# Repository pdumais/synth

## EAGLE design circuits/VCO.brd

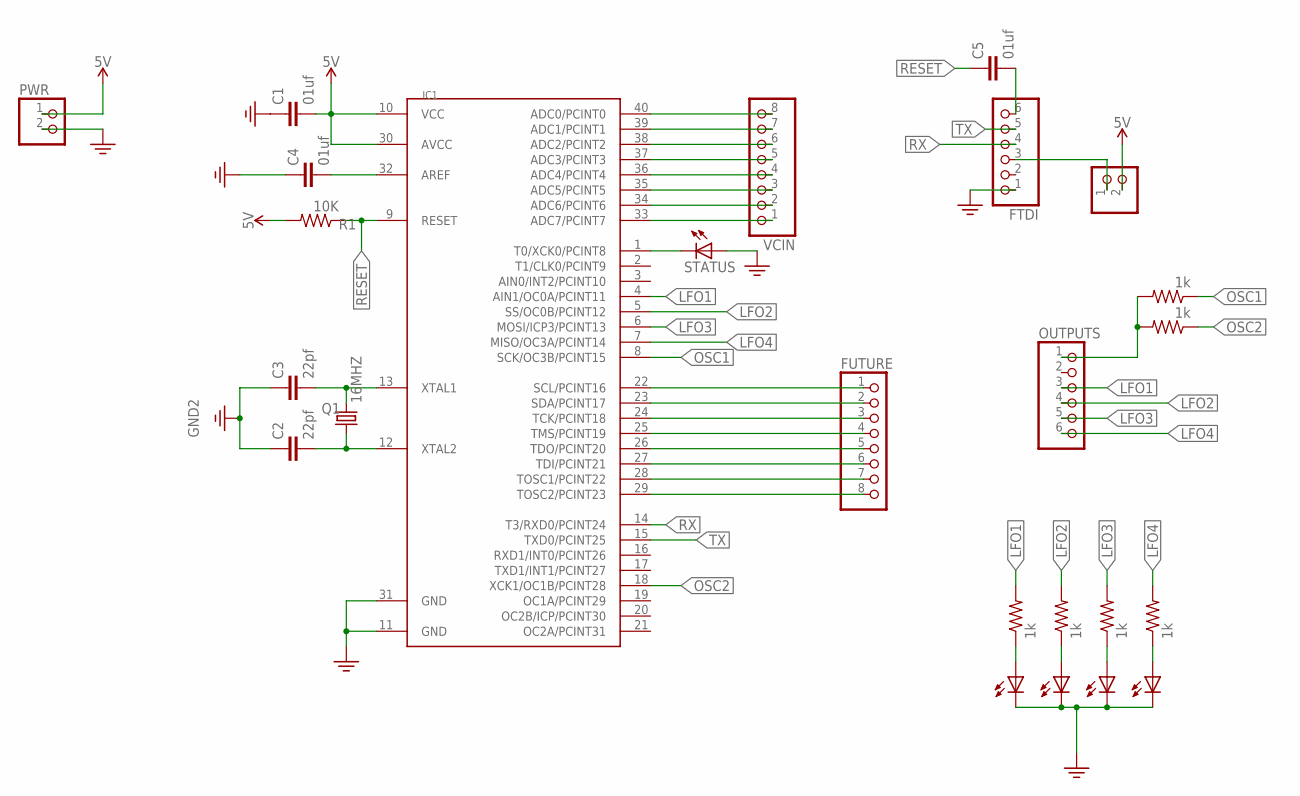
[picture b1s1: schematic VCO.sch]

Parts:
C1, C4, C5: 01uf; C025-024X044
C2, C3: 22pf; C025-024X044
FTDI: PINHD-1X6; 1X06
FUTURE: PINHD-1X8BIG; 1X08-BIG
IC1: MEGA1284P; DIL40
LFO1, LFO2, LFO3, LFO4: LED5MM
OUTPUTS: PINHD-1X6; 1X06
PWR, PWR1: PINHD-1X2; 1X02
Q1: 16MHZ; HC49/S
R1: 10K; 0207/12
R2, R3, R4, R5, R6, R7: 1k; 0207/12
STATUS: LED5MM
VCIN: PINHD-1X8; 1X08

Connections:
3.3V: C1.1, C2.1, C3.1, C4.1, FTDI.1, IC1.11 (GND), IC1.31 (GND), LFO1.K (C), LFO2.K (C), LFO3.K (C), LFO4.K (C), PWR.2, STATUS.A
LFO1: IC1.4 (AIN1/OC0A/PCINT11), OUTPUTS.3, R4.2
LFO2: IC1.5 (SS/OC0B/PCINT12), OUTPUTS.4, R3.2
LFO3: IC1.6 (MOSI/ICP3/PCINT13), OUTPUTS.5, R2.2
LFO4: IC1.7 (MISO/OC3A/PCINT14), OUTPUTS.6, R5.2
unnamed: LFO1.A, R4.1
unnamed: IC1.40 (ADC0/PCINT0), VCIN.8
unnamed: IC1.39 (ADC1/PCINT1), VCIN.7
unnamed: IC1.38 (ADC2/PCINT2), VCIN.6
unnamed: IC1.37 (ADC3/PCINT3), VCIN.5
unnamed: IC1.36 (ADC4/PCINT4), VCIN.4
unnamed: IC1.35 (ADC5/PCINT5), VCIN.3
unnamed: IC1.34 (ADC6/PCINT6), VCIN.2
unnamed: IC1.33 (ADC7/PCINT7), VCIN.1
unnamed: C3.2, IC1.13 (XTAL1), Q1.2
unnamed: C2.2, IC1.12 (XTAL2), Q1.1
unnamed: LFO2.A, R3.1
unnamed: C4.2, IC1.32 (AREF)
unnamed: C5.2, FTDI.6
unnamed: LFO3.A, R2.1
unnamed: LFO4.A, R5.1
unnamed: OUTPUTS.1, R6.2, R7.2
unnamed: FUTURE.1, IC1.22 (SCL/PCINT16)
unnamed: FUTURE.2, IC1.23 (SDA/PCINT17)
unnamed: FUTURE.3, IC1.24 (TCK/PCINT18)
unnamed: FUTURE.4, IC1.25 (TMS/PCINT19)
unnamed: FUTURE.5, IC1.26 (TDO/PCINT20)
unnamed: FTDI.3, PWR1.1
unnamed: IC1.1 (T0/XCK0/PCINT8), STATUS.K (C)
unnamed: FUTURE.6, IC1.27 (TDI/PCINT21)
unnamed: FUTURE.7, IC1.28 (TOSC1/PCINT22)
unnamed: FUTURE.8, IC1.29 (TOSC2/PCINT23)
OSC1: IC1.8 (SCK/OC3B/PCINT15), R6.1
OSC2: IC1.18 (XCK1/OC1B/PCINT28), R7.1
RESET: C5.1, IC1.9 (RESET), R1.1
RX: FTDI.4, IC1.14 (T3/RXD0/PCINT24)
TX: FTDI.5, IC1.15 (TXD0/PCINT25)
VDD: C1.2, IC1.10 (VCC), IC1.30 (AVCC), PWR.1, PWR1.2, R1.2

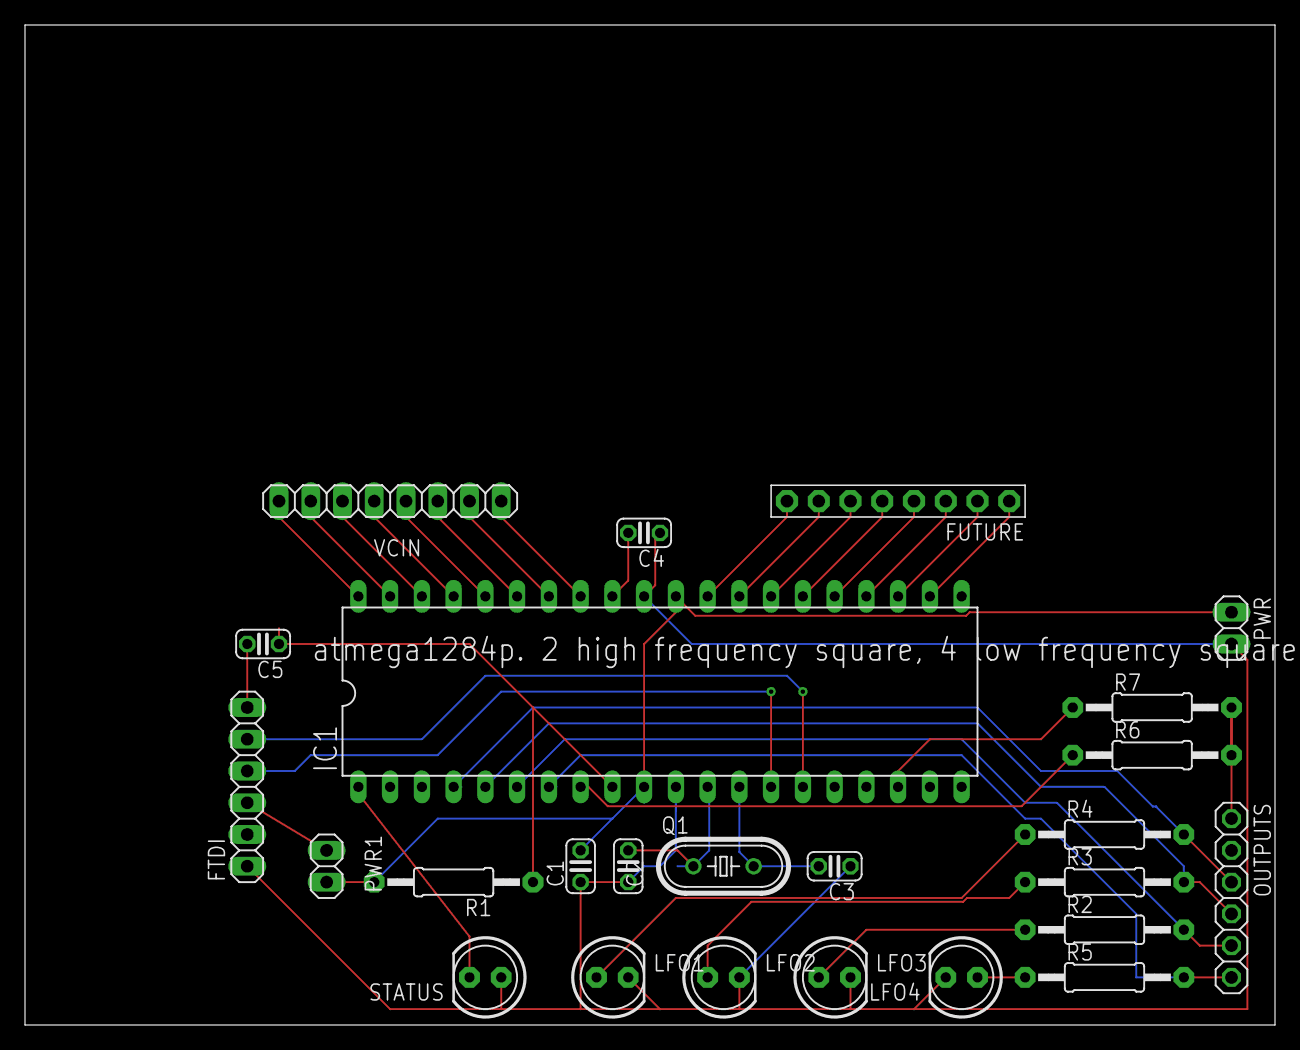
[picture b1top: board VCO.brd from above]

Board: 2 copper layers, 100.0 x 80.0 mm, 25 parts (0 on the bottom side), 38 nets.

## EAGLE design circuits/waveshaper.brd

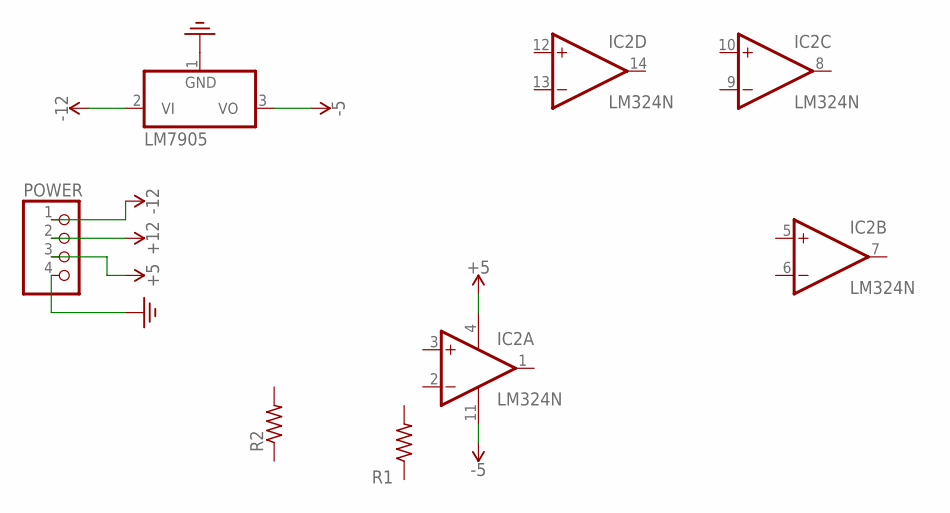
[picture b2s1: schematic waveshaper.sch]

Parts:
IC2: LM324N; DIL14
LM7905: 7905T; TO220H
POWER: PINHD-1X4; 1X04
R1, R2: R-US_0207/12; 0207/12

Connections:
3.3V: LM7905.1 (GND), POWER.4
VDD: IC2.4 (V+), IC2.11 (V-), LM7905.2 (VI), LM7905.3 (VO), POWER.1, POWER.2, POWER.3

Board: 2 copper layers, 5 parts (0 on the bottom side), 2 nets, no tracks yet.

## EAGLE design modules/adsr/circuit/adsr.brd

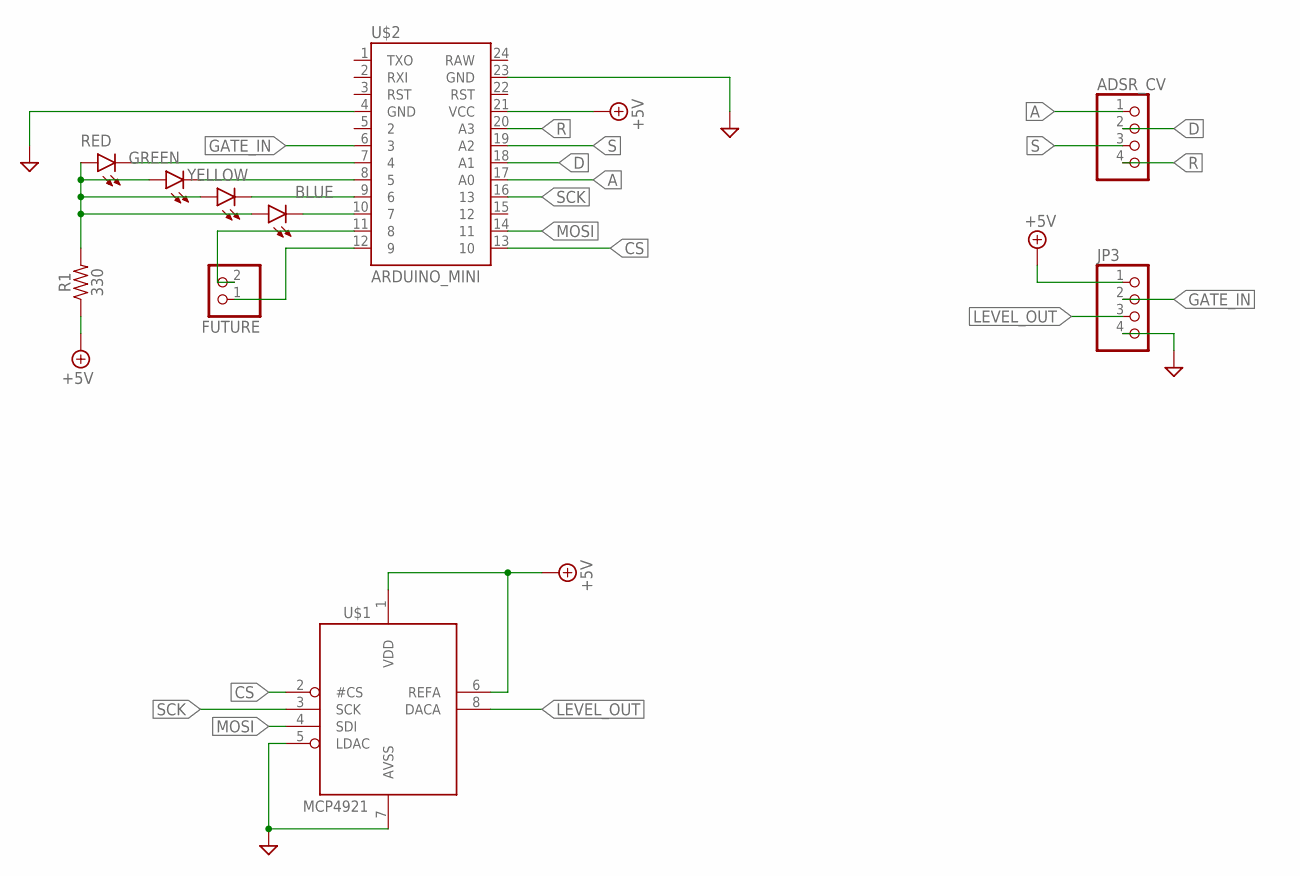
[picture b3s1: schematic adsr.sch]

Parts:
ADSR_CV: PINHD-1X4; 1X04
BLUE: LED-5MM-KIT-NO-SILK; LED_5MM-KIT-NO-SILK
FUTURE: PINHD-1X2; 1X02
GREEN: LED-5MM-KIT-NO-SILK; LED_5MM-KIT-NO-SILK
JP3: PINHD-1X4; 1X04
R1: 330; AXIAL-0.3
RED: LED-5MM-KIT-NO-SILK; LED_5MM-KIT-NO-SILK
U$1: MCP4921; DIL08
U$2: ARDUINO_MINI
YELLOW: LED-5MM-KIT-NO-SILK; LED_5MM-KIT-NO-SILK

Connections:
+5V: JP3.1, R1.P$1 (1), U$1.1 (VDD), U$1.6 (REFA), U$2.21 (VCC)
A: ADSR_CV.1, U$2.17 (A0)
CS: U$1.2 (#CS), U$2.13 (10)
D: ADSR_CV.2, U$2.18 (A1)
GATE_IN: JP3.2, U$2.6 (3)
GND: JP3.4, U$1.5 (LDAC), U$1.7 (AVSS), U$2.4 (GND), U$2.23 (GND)
LEVEL_OUT: JP3.3, U$1.8 (DACA)
MOSI: U$1.4 (SDI), U$2.14 (11)
unnamed: BLUE.K (C), U$2.10 (7)
unnamed: U$2.9 (6), YELLOW.K (C)
unnamed: GREEN.K (C), U$2.8 (5)
unnamed: RED.K (C), U$2.7 (4)
unnamed: BLUE.A, GREEN.A, R1.P$2 (2), RED.A, YELLOW.A
unnamed: FUTURE.2, U$2.11 (8)
unnamed: FUTURE.1, U$2.12 (9)
R: ADSR_CV.4, U$2.20 (A3)
S: ADSR_CV.3, U$2.19 (A2)
SCK: U$1.3 (SCK), U$2.16 (13)

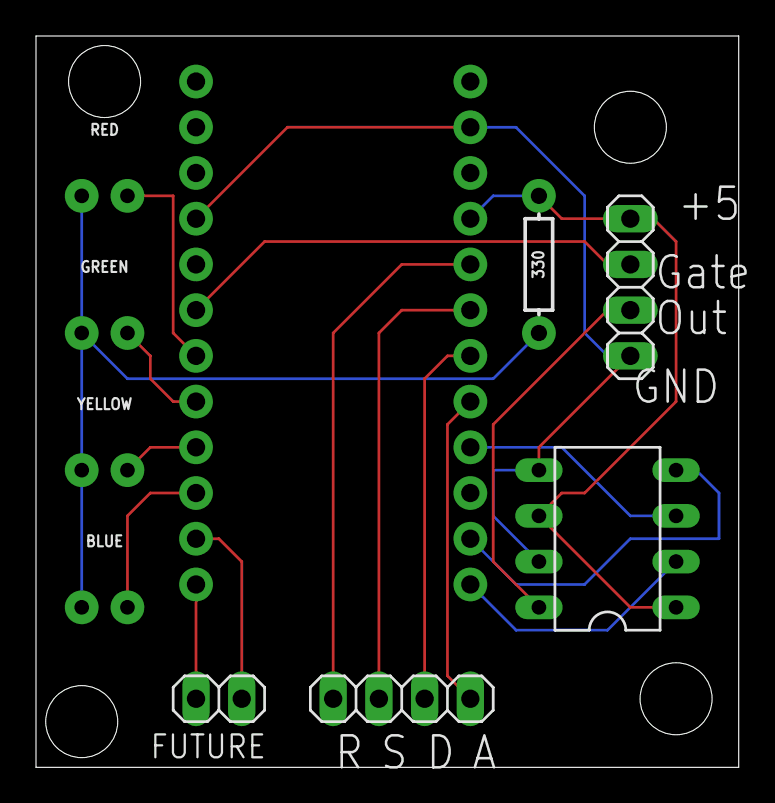
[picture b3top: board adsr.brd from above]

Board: 2 copper layers, 39.0 x 40.6 mm, 10 parts (0 on the bottom side), 18 nets.

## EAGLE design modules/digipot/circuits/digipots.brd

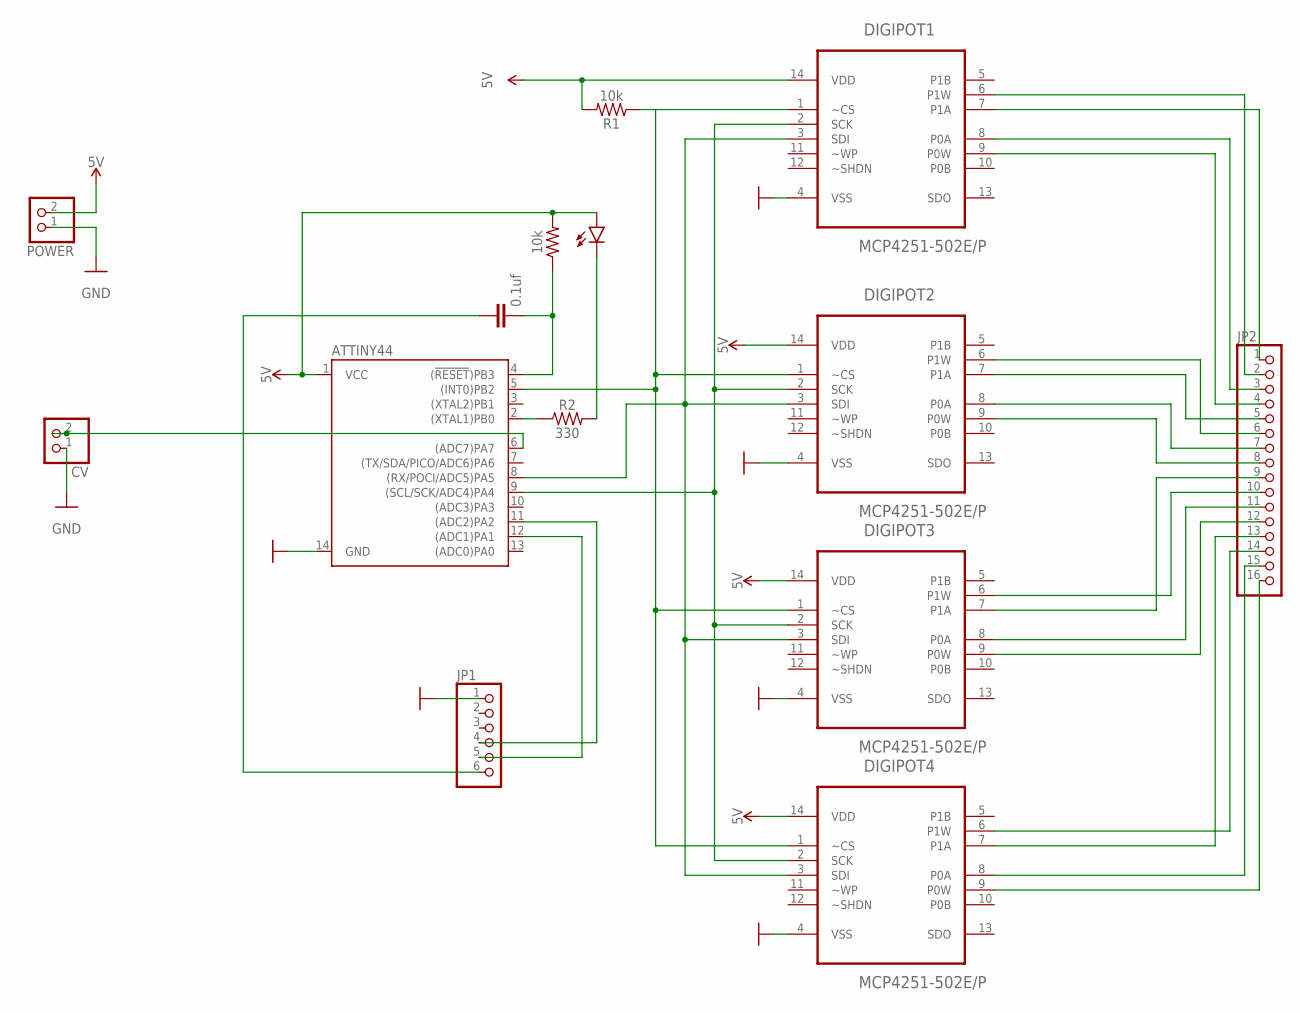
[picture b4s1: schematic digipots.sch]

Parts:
ATTINY44: ATTINY84ATTINY84-20PU; DIP14
C2: 0.1uf; C025-024X044
CV: PINHD-1X2; 1X02
D1: LED-5MM-KIT-NO-SILK; LED_5MM-KIT-NO-SILK
DIGIPOT1, DIGIPOT2, DIGIPOT3, DIGIPOT4: MCP4251-502E/P; DIP254P762X533-14
JP1: PINHD-1X6; 1X06
JP2: PINHD-1X16; 1X16
POWER: PINHD-1X2; 1X02
R1, R3: 10k; AXIAL-0.3
R2: 330; AXIAL-0.3

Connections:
5V: ATTINY44.1 (VCC), D1.A, DIGIPOT1.14 (VDD), DIGIPOT2.14 (VDD), DIGIPOT3.14 (VDD), DIGIPOT4.14 (VDD), POWER.2, R1.P$2 (2), R3.P$2 (2)
GND: ATTINY44.14 (GND), CV.1, DIGIPOT1.4 (VSS), DIGIPOT2.4 (VSS), DIGIPOT3.4 (VSS), DIGIPOT4.4 (VSS), JP1.1, POWER.1
unnamed: DIGIPOT4.9 (P0W), JP2.16
unnamed: DIGIPOT4.8 (P0A), JP2.15
unnamed: DIGIPOT4.6 (P1W), JP2.14
unnamed: DIGIPOT4.7 (P1A), JP2.13
unnamed: DIGIPOT3.9 (P0W), JP2.12
unnamed: DIGIPOT3.8 (P0A), JP2.11
unnamed: DIGIPOT3.6 (P1W), JP2.10
unnamed: DIGIPOT3.7 (P1A), JP2.9
unnamed: DIGIPOT2.9 (P0W), JP2.8
unnamed: DIGIPOT2.8 (P0A), JP2.7
unnamed: DIGIPOT2.7 (P1A), JP2.5
unnamed: DIGIPOT2.6 (P1W), JP2.6
unnamed: DIGIPOT1.9 (P0W), JP2.4
unnamed: DIGIPOT1.8 (P0A), JP2.3
unnamed: DIGIPOT1.7 (P1A), JP2.1
unnamed: DIGIPOT1.6 (P1W), JP2.2
unnamed: ATTINY44.5 ((INT0)PB2), DIGIPOT1.1 (~CS), DIGIPOT2.1 (~CS), DIGIPOT3.1 (~CS), DIGIPOT4.1 (~CS), R1.P$1 (1)
unnamed: ATTINY44.9 ((SCL/SCK/ADC4)PA4), DIGIPOT1.2 (SCK), DIGIPOT2.2 (SCK), DIGIPOT3.2 (SCK), DIGIPOT4.2 (SCK)
unnamed: ATTINY44.2 ((XTAL1)PB0), R2.P$1 (1)
unnamed: ATTINY44.8 ((RX/POCI/ADC5)PA5), DIGIPOT1.3 (SDI), DIGIPOT2.3 (SDI), DIGIPOT3.3 (SDI), DIGIPOT4.3 (SDI)
unnamed: D1.K (C), R2.P$2 (2)
unnamed: ATTINY44.4 ((!RESET!)PB3), C2.2, R3.P$1 (1)
unnamed: ATTINY44.12 ((ADC1)PA1), JP1.5
unnamed: C2.1, JP1.6
unnamed: ATTINY44.11 ((ADC2)PA2), JP1.4
unnamed: ATTINY44.6 ((ADC7)PA7), CV.2

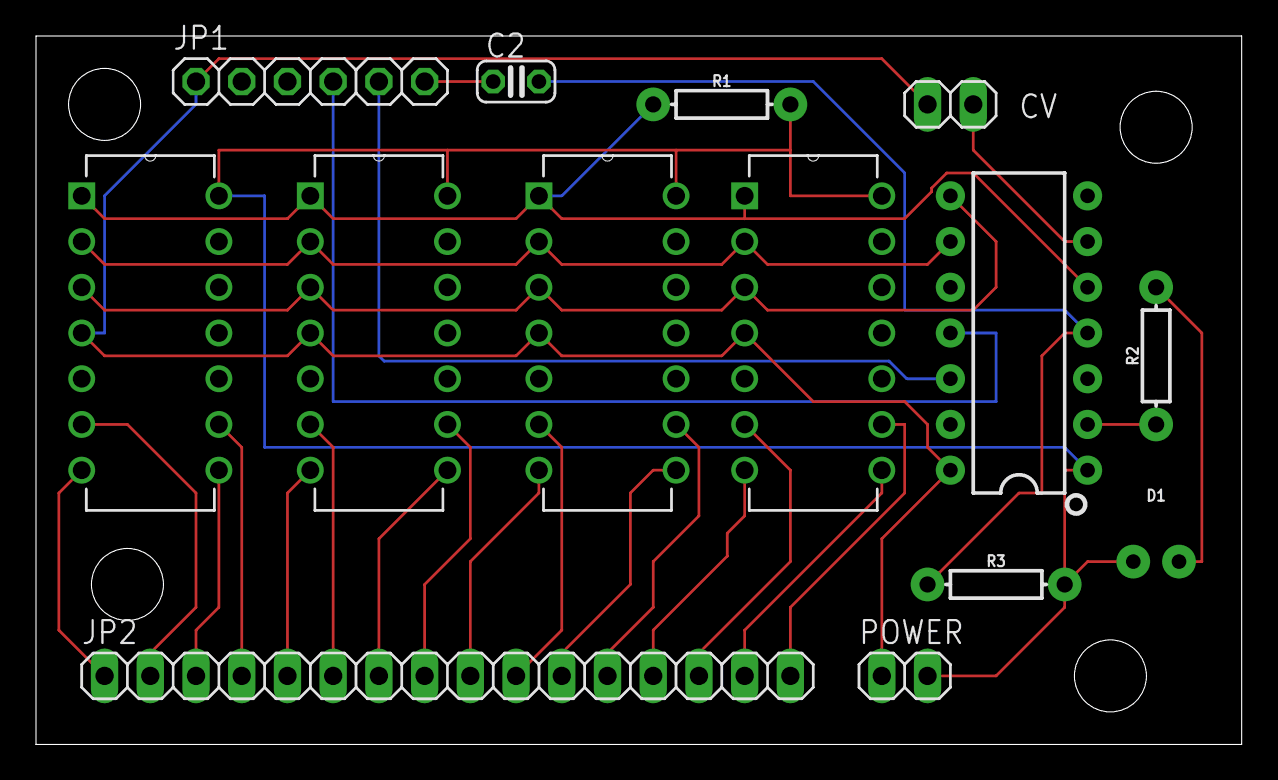
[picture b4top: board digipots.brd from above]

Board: 2 copper layers, 67.0 x 39.4 mm, 14 parts (0 on the bottom side), 28 nets.

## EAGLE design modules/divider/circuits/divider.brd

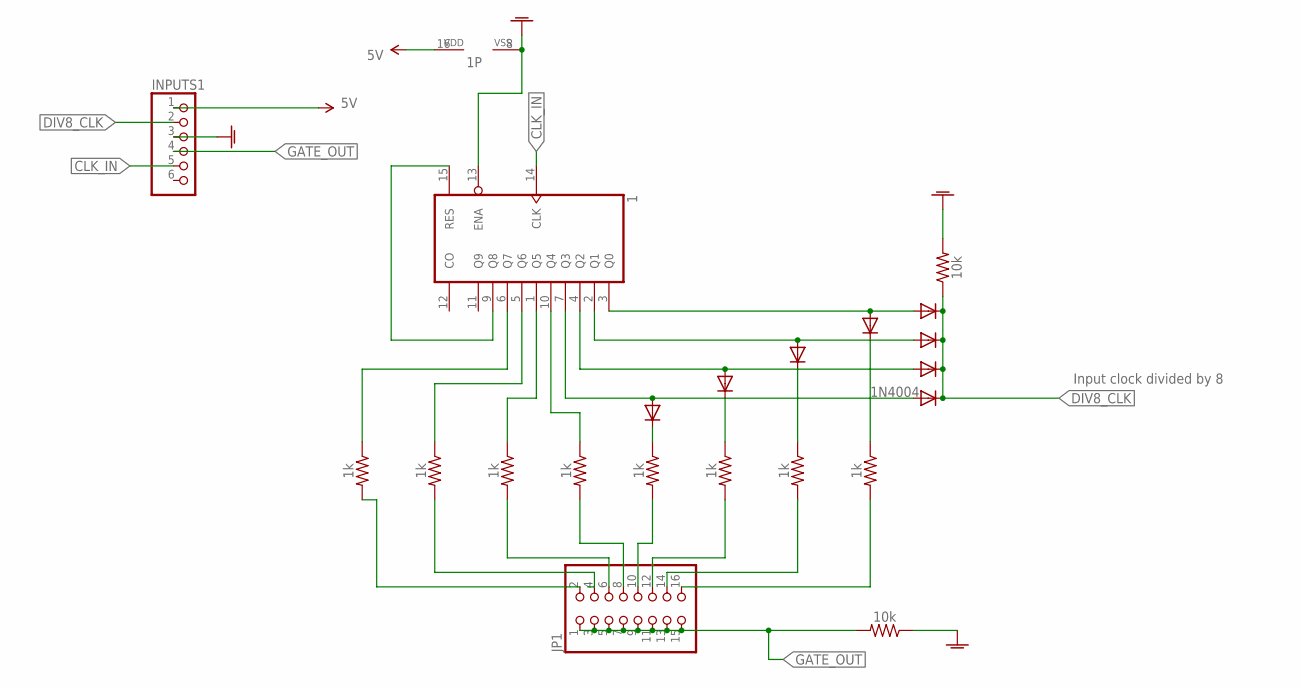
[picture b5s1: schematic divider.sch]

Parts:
1: 4017N; DIL16
D9, D10, D11, D12, D13, D14, D15, D16: 1N4004; DO41-10
INPUTS1: PINHD-1X6; 1X06
JP1: PINHD-2X8; 2X08
R40, R56: 10k; AXIAL-0.3
R48, R49, R50, R51, R52, R53, R54, R55: 1k; AXIAL-0.3

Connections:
5V: 1.16 (VDD), INPUTS1.1
CLK_IN: 1.14 (CLK), INPUTS1.5
DIV8_CLK: D9.C, D10.C, D11.C, D12.C, INPUTS1.2, R40.P$1 (1)
GATE_OUT: INPUTS1.4, JP1.1, JP1.3, JP1.5, JP1.7, JP1.9, JP1.11, JP1.13, JP1.15, R56.P$2 (2)
GND: 1.8 (VSS), 1.13 (ENA)
GNDA: INPUTS1.3, R40.P$2 (2), R56.P$1 (1)
unnamed: JP1.4, R49.P$2 (2)
unnamed: JP1.2, R48.P$2 (2)
unnamed: 1.9 (Q8), 1.15 (RES)
unnamed: 1.3 (Q0), D9.A, D16.A
unnamed: 1.2 (Q1), D10.A, D13.A
unnamed: 1.4 (Q2), D11.A, D14.A
unnamed: 1.7 (Q3), D12.A, D15.A
unnamed: 1.6 (Q7), R48.P$1 (1)
unnamed: JP1.6, R50.P$2 (2)
unnamed: 1.10 (Q4), R51.P$1 (1)
unnamed: JP1.10, R52.P$2 (2)
unnamed: JP1.12, R53.P$2 (2)
unnamed: JP1.14, R54.P$2 (2)
unnamed: JP1.16, R55.P$2 (2)
unnamed: 1.5 (Q6), R49.P$1 (1)
unnamed: 1.1 (Q5), R50.P$1 (1)
unnamed: JP1.8, R51.P$2 (2)
unnamed: D15.C, R52.P$1 (1)
unnamed: D14.C, R53.P$1 (1)
unnamed: D13.C, R54.P$1 (1)
unnamed: D16.C, R55.P$1 (1)

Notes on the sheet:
Input clock divided by 8

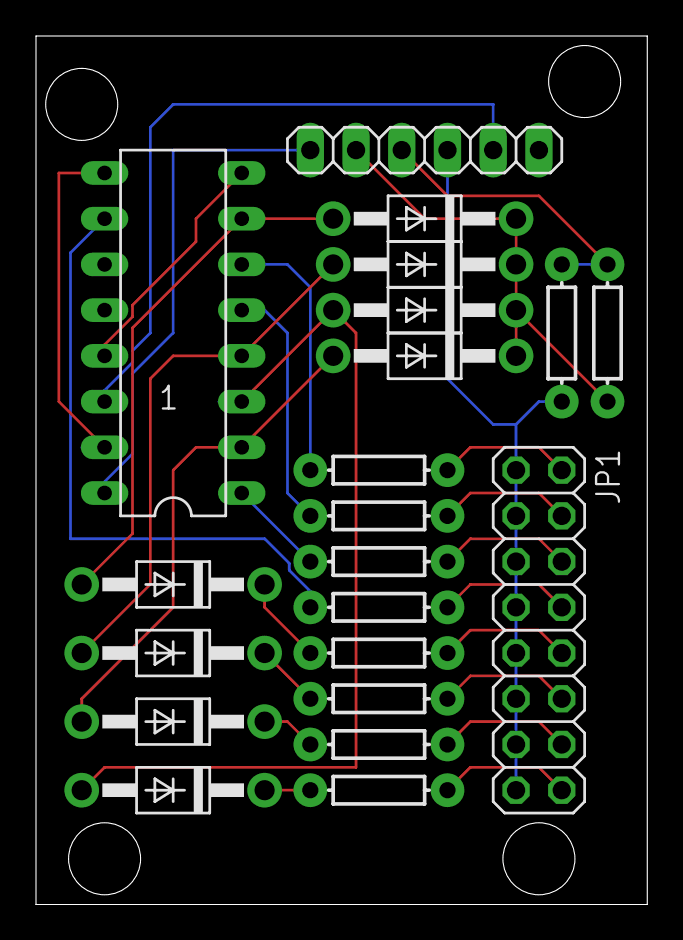
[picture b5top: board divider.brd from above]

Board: 2 copper layers, 34.0 x 48.2 mm, 21 parts (0 on the bottom side), 27 nets.

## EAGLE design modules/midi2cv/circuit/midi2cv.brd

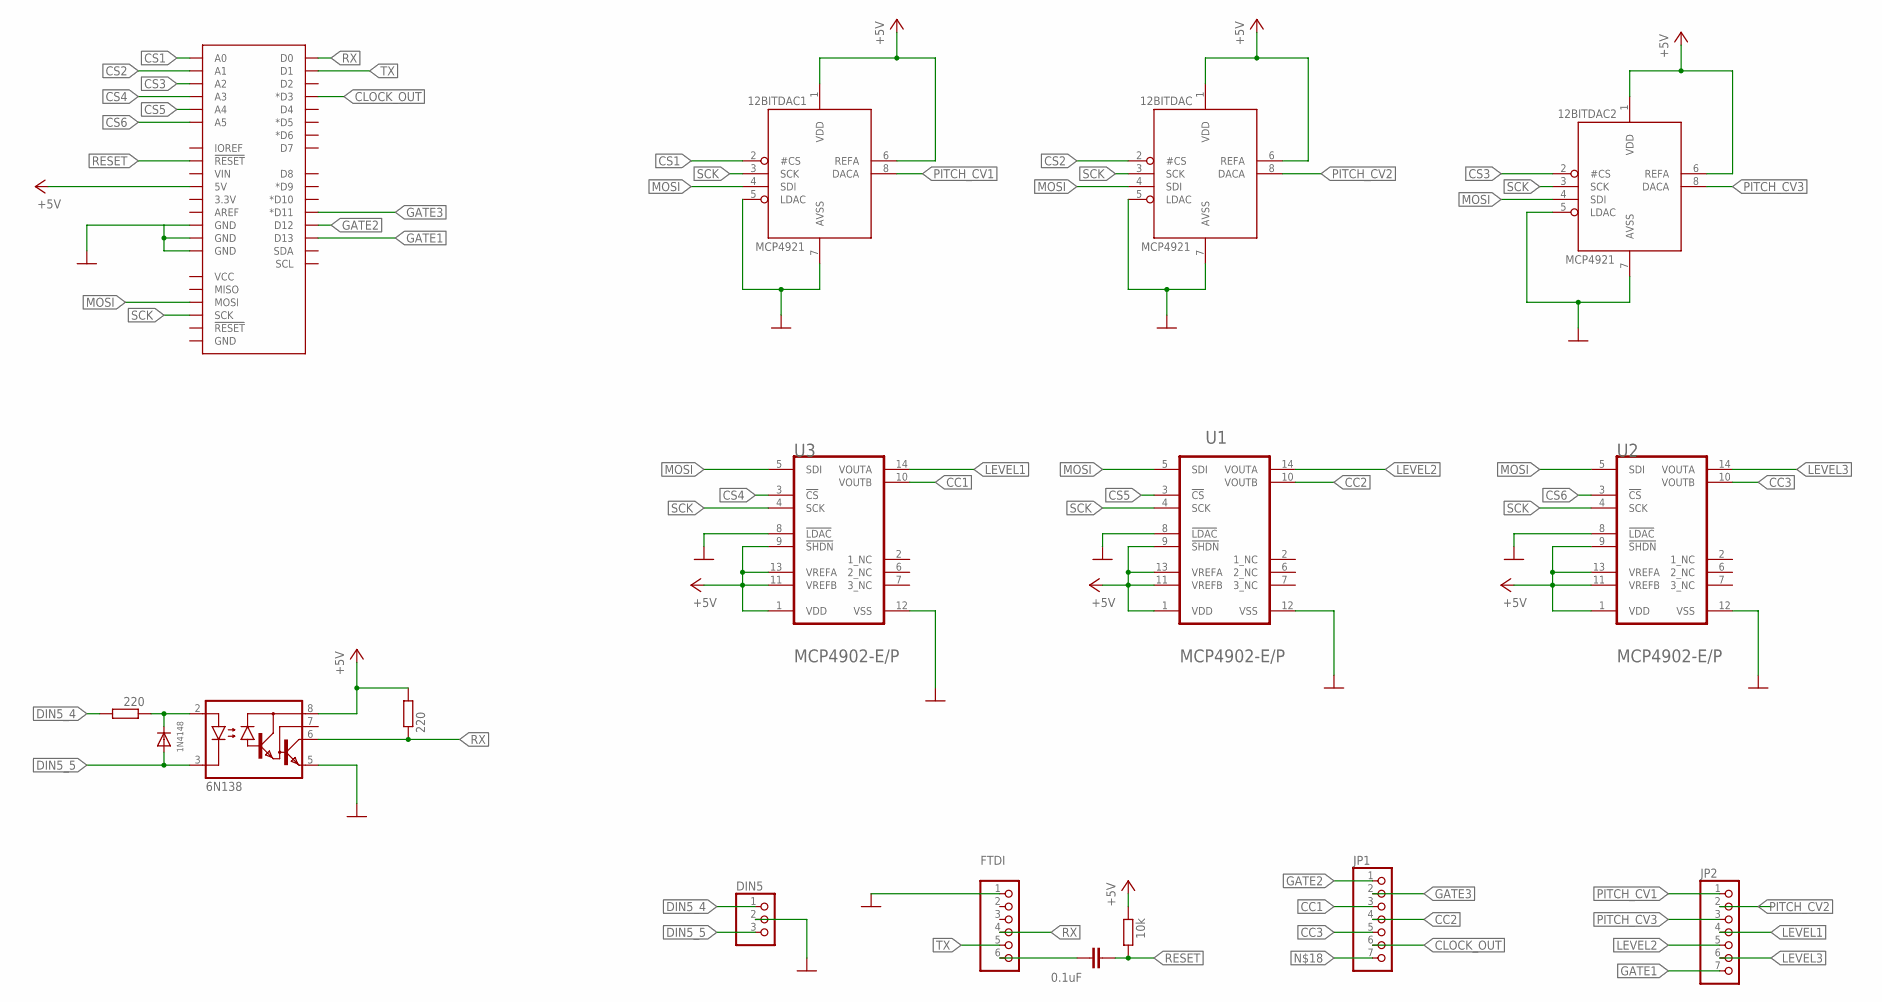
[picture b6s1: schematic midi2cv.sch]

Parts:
12BITDAC, 12BITDAC1, 12BITDAC2: MCP4921; DIL08
B1: ARDUINO_UNO_R3_SHIELD_ICSP-NO_LABELS; UNO_R3_SHIELD_ICSP_NOLABELS
C1: 0.1uF; CAP-PTH-SMALL-KIT
D1: 1N4148; DO-1N4148
DIN5: PINHD-1X3; 1X03
FTDI: PINHD-1X6; 1X06
JP1, JP2: PINHD-1X7; 1X07
OK1: 6N138; DIL08
R2, R3: 220; 0207/10
R4: 10k; 0207/10
U1, U2, U3: MICROCHIP_MCP4902-E-PMICROCHIP_MCP4902-E-P_0_0; MICROCHIP_MCP4902-E-P_0

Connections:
+5V: 12BITDAC.1 (VDD), 12BITDAC.6 (REFA), 12BITDAC1.1 (VDD), 12BITDAC1.6 (REFA), 12BITDAC2.1 (VDD), 12BITDAC2.6 (REFA), B1.5V, OK1.8 (VCC), R2.2, R4.2, U1.1 (VDD), U1.9 (!SHDN!), U1.11 (VREFB), U1.13 (VREFA), U2.1 (VDD), U2.9 (!SHDN!), U2.11 (VREFB), U2.13 (VREFA), U3.1 (VDD), U3.9 (!SHDN!), U3.11 (VREFB), U3.13 (VREFA)
CC1: JP1.3, U3.10 (VOUTB)
CC2: JP1.4, U1.10 (VOUTB)
CC3: JP1.5, U2.10 (VOUTB)
CLOCK_OUT: B1.D3 (*D3), JP1.6
CS1: 12BITDAC1.2 (#CS), B1.A0
CS2: 12BITDAC.2 (#CS), B1.A1
CS3: 12BITDAC2.2 (#CS), B1.A2
CS4: B1.A3, U3.3 (!CS!)
CS5: B1.A4, U1.3 (!CS!)
CS6: B1.A5, U2.3 (!CS!)
DIN5_4: DIN5.1, R3.2
DIN5_5: D1.A, DIN5.3, OK1.3 (C)
GATE1: B1.D13, JP2.7
GATE2: B1.D12, JP1.1
GATE3: B1.D11 (*D11), JP1.2
GND: 12BITDAC.5 (LDAC), 12BITDAC.7 (AVSS), 12BITDAC1.5 (LDAC), 12BITDAC1.7 (AVSS), 12BITDAC2.5 (LDAC), 12BITDAC2.7 (AVSS), B1.GND@0 (GND), B1.GND@1 (GND), B1.GND@2 (GND), DIN5.2, FTDI.1, OK1.5 (GND), U1.8 (!LDAC!), U1.12 (VSS), U2.8 (!LDAC!), U2.12 (VSS), U3.8 (!LDAC!), U3.12 (VSS)
LEVEL1: JP2.4, U3.14 (VOUTA)
LEVEL2: JP2.5, U1.14 (VOUTA)
LEVEL3: JP2.6, U2.14 (VOUTA)
MOSI: 12BITDAC.4 (SDI), 12BITDAC1.4 (SDI), 12BITDAC2.4 (SDI), B1.MOSI, U1.5 (SDI), U2.5 (SDI), U3.5 (SDI)
unnamed: D1.C, OK1.2 (A), R3.1
unnamed: C1.1, FTDI.6
PITCH_CV1: 12BITDAC1.8 (DACA), JP2.1
PITCH_CV2: 12BITDAC.8 (DACA), JP2.2
PITCH_CV3: 12BITDAC2.8 (DACA), JP2.3
RESET: B1.RES (!RESET!), C1.2, R4.1
RX: B1.RX (D0), FTDI.4, OK1.6 (VO), R2.1
SCK: 12BITDAC.3 (SCK), 12BITDAC1.3 (SCK), 12BITDAC2.3 (SCK), B1.SCK, U1.4 (SCK), U2.4 (SCK), U3.4 (SCK)
TX: B1.TX (D1), FTDI.5

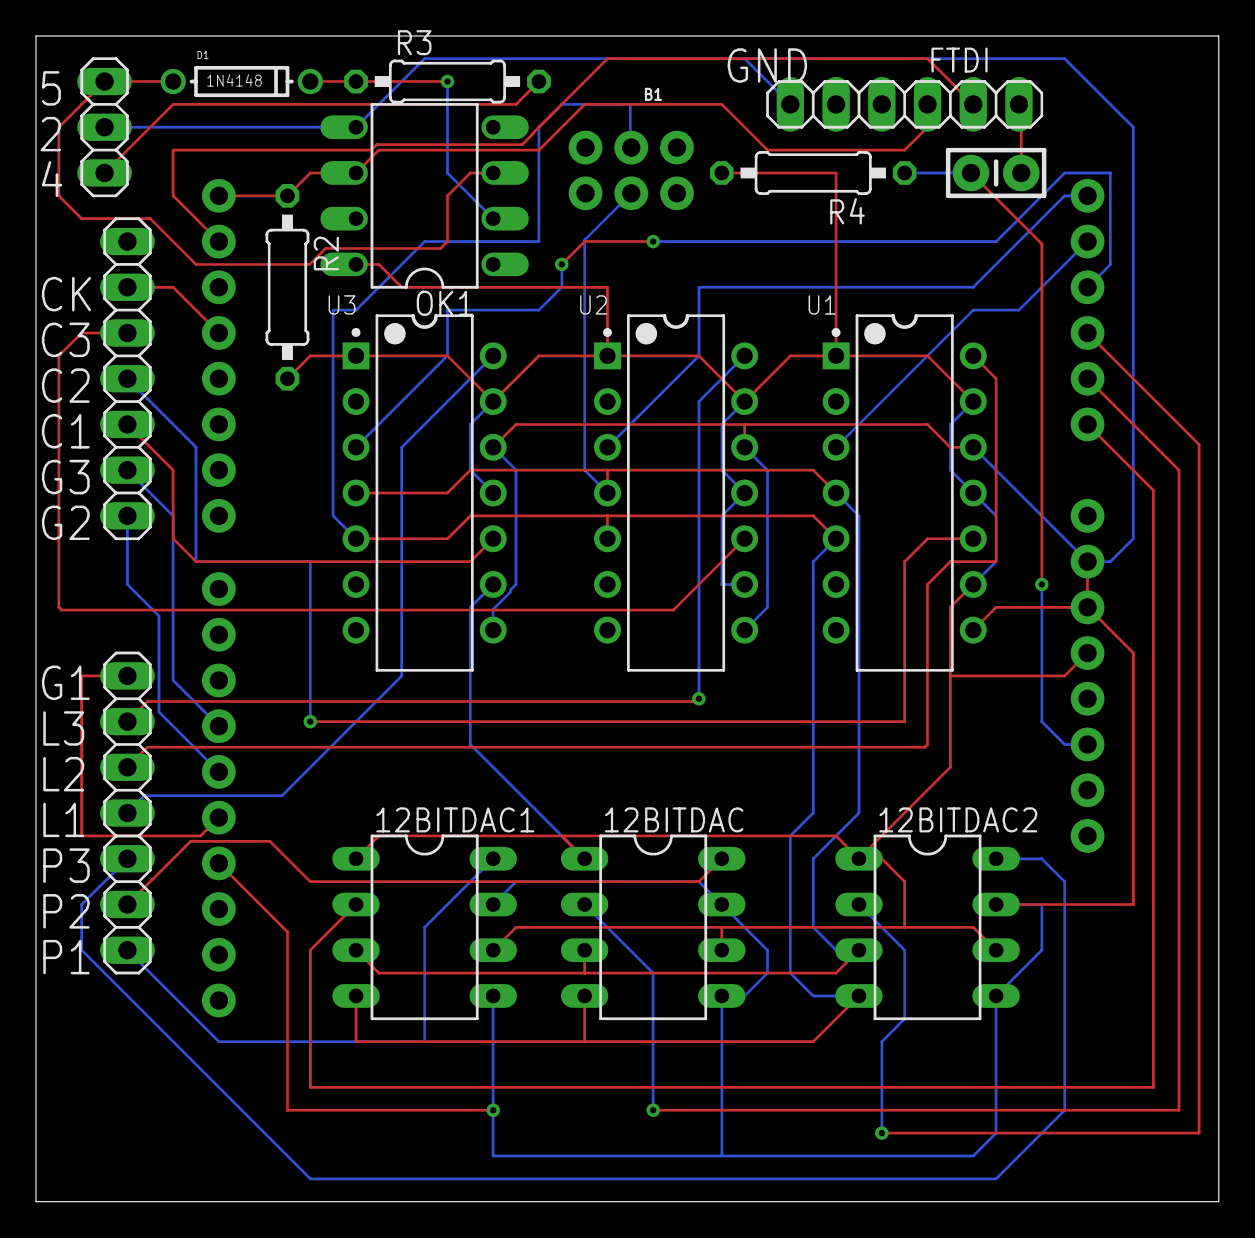
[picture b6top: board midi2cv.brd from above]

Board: 2 copper layers, 65.7 x 64.8 mm, 17 parts (0 on the bottom side), 30 nets.

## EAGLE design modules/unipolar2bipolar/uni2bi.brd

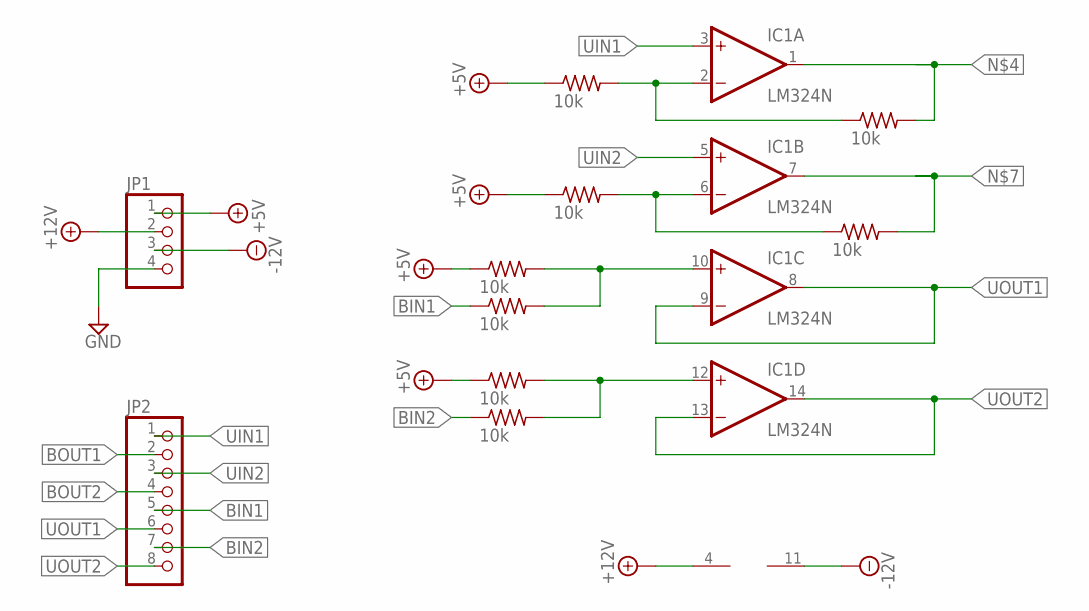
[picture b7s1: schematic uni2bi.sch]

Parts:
IC1: LM324N; DIL14
JP1: PINHD-1X4; 1X04
JP2: PINHD-1X8; 1X08
R3, R4, R5, R6, R7, R8, R9, R10: 10k; 0207/10

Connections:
+5V: JP1.1, R3.1, R7.1, R8.1, R9.1
+12V: IC1.4 (V+), JP1.2
-12V: IC1.11 (V-), JP1.3
BIN1: JP2.5, R4.1
BIN2: JP2.7, R5.1
BOUT1: IC1.2 (-IN), JP2.2, R8.2, R10.1
BOUT2: IC1.6 (-IN), JP2.4, R6.1, R7.2
GND: JP1.4
unnamed: IC1.10 (+IN), R4.2, R9.2
unnamed: IC1.12 (+IN), R3.2, R5.2
unnamed: IC1.1 (OUT), R10.2
unnamed: IC1.7 (OUT), R6.2
UIN1: IC1.3 (+IN), JP2.1
UIN2: IC1.5 (+IN), JP2.3
UOUT1: IC1.8 (OUT), IC1.9 (-IN), JP2.6
UOUT2: IC1.13 (-IN), IC1.14 (OUT), JP2.8

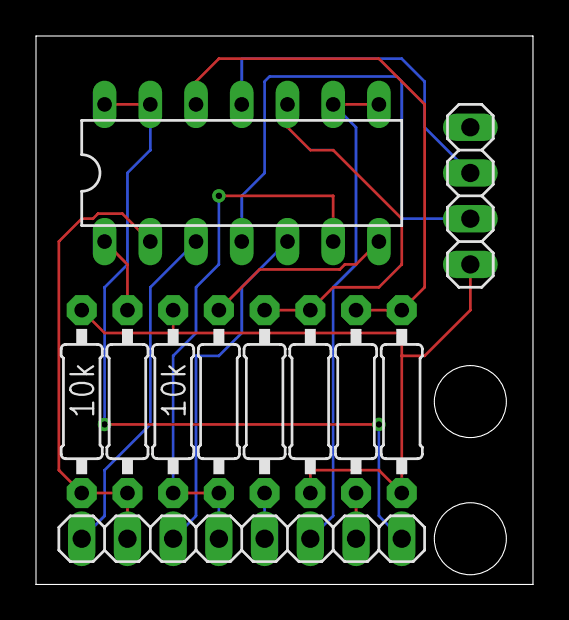
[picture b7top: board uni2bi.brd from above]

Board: 2 copper layers, 27.6 x 30.5 mm, 11 parts (0 on the bottom side), 15 nets.

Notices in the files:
parts and their libraries:
SparkFun-PowerSymbols: Licensing: Creative Commons ShareAlike 4.0 International - https://creativecommons.org/licenses/by-sa/4.0
